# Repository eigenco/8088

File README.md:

# 8088
Modular standalone 8088 boards and BIOS.

There might be some redundancy that will be fixed later. 

Demo:  https://www.youtube.com/watch?v=A7xD_wg7Bzw

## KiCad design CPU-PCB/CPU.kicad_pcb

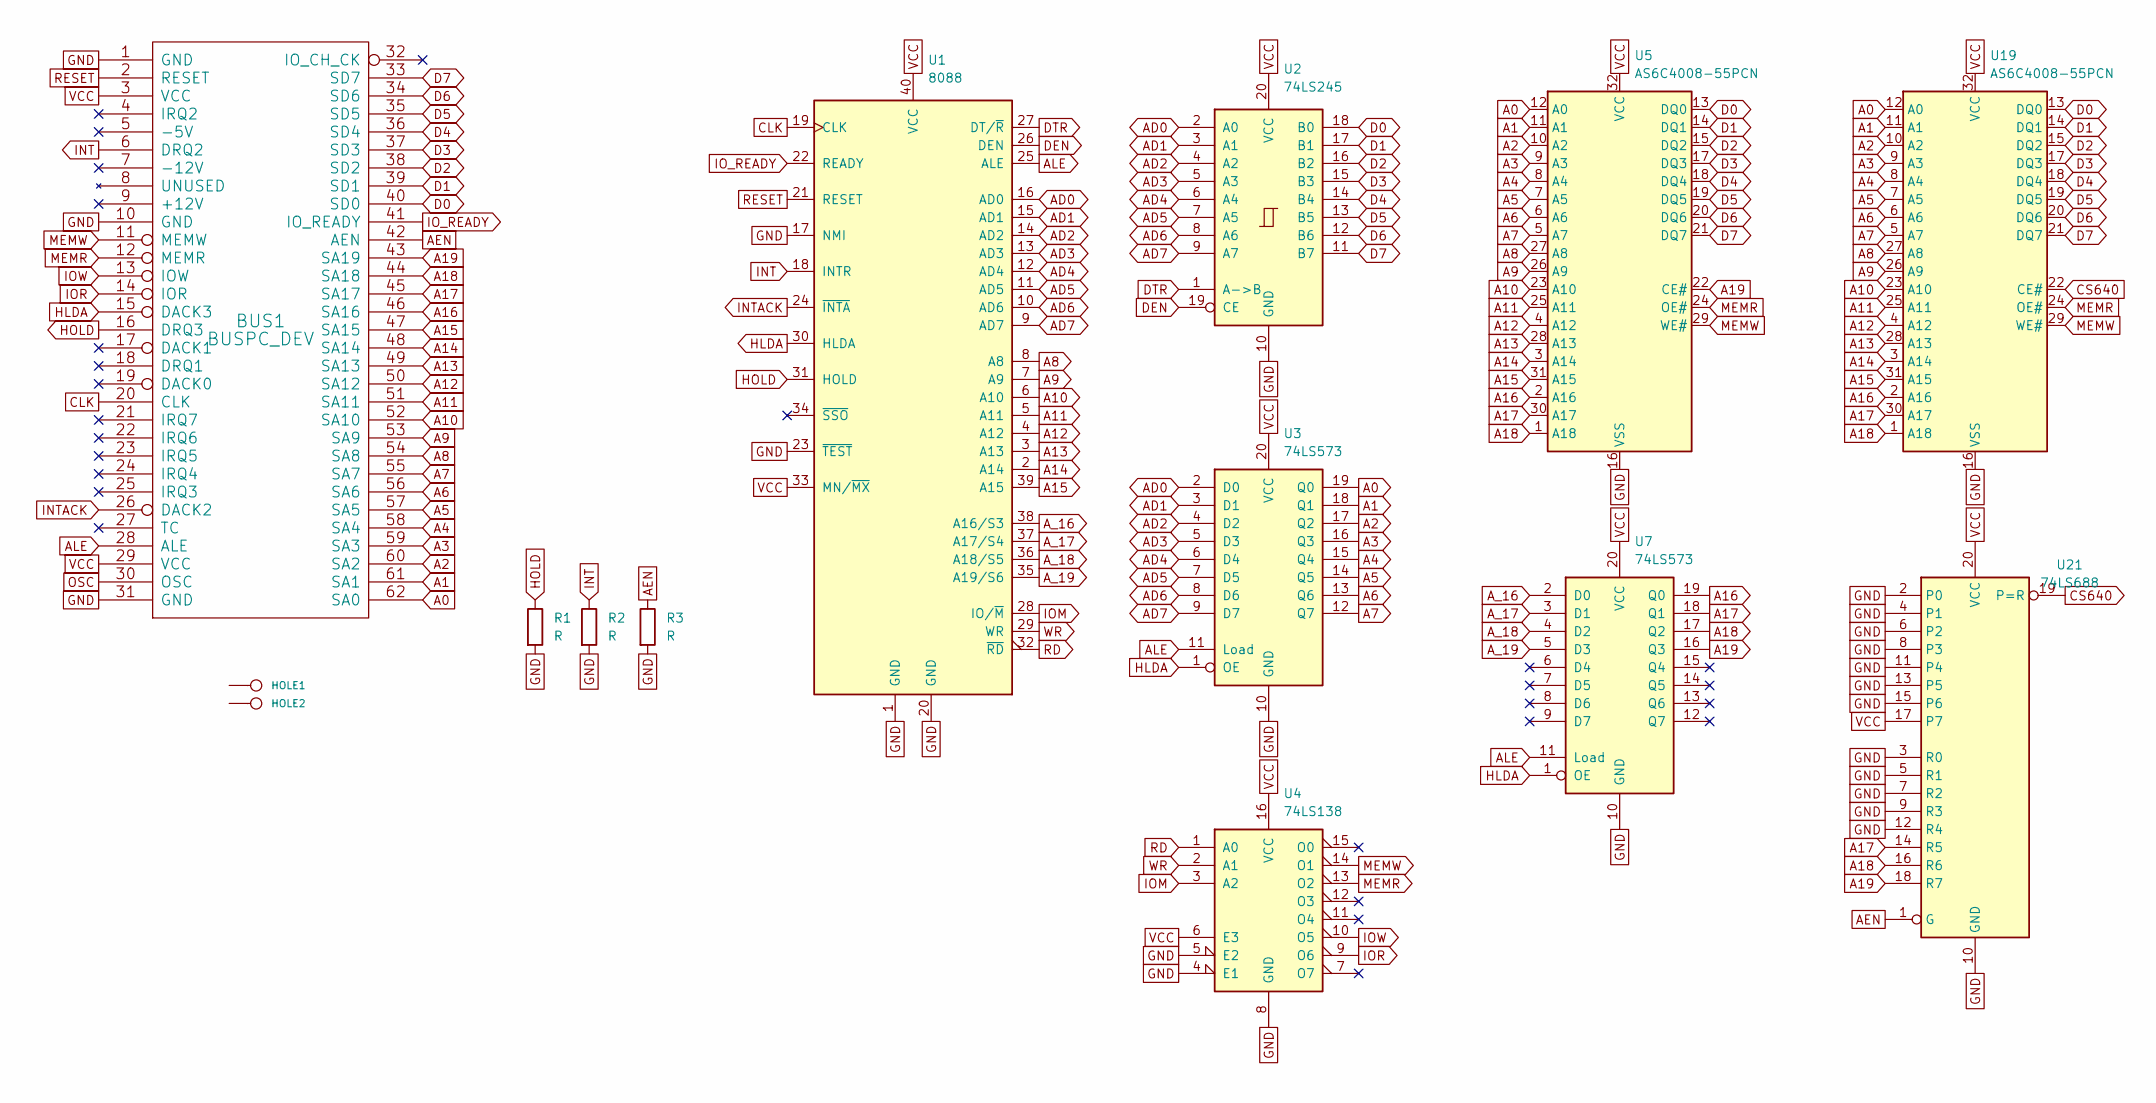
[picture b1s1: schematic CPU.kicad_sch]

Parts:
BUS1: BUSPC_DEV; Conn_Bus_ISA8
HOLE1, HOLE2: CONN_1; HOLE_3MM
R1, R2, R3: R; R_0201_0603Metric
U1: 8088; DIP-40_W15.24mm
U2: 74LS245; DIP-20_W7.62mm_Socket
U3, U7: 74LS573; DIP-20_W7.62mm_Socket
U4: 74LS138; DIP-16_W7.62mm_Socket
U5, U19: AS6C4008-55PCN; DIP-32_W15.24mm
U21: 74LS688; DIP-20_W7.62mm_Socket

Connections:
A0: BUS1.62 (SA0), U3.19 (Q0), U5.12 (A0), U19.12 (A0)
A1: BUS1.61 (SA1), U3.18 (Q1), U5.11 (A1), U19.11 (A1)
A2: BUS1.60 (SA2), U3.17 (Q2), U5.10 (A2), U19.10 (A2)
A3: BUS1.59 (SA3), U3.16 (Q3), U5.9 (A3), U19.9 (A3)
A4: BUS1.58 (SA4), U3.15 (Q4), U5.8 (A4), U19.8 (A4)
A5: BUS1.57 (SA5), U3.14 (Q5), U5.7 (A5), U19.7 (A5)
A6: BUS1.56 (SA6), U3.13 (Q6), U5.6 (A6), U19.6 (A6)
A7: BUS1.55 (SA7), U3.12 (Q7), U5.5 (A7), U19.5 (A7)
A8: BUS1.54 (SA8), U1.8 (A8), U5.27 (A8), U19.27 (A8)
A9: BUS1.53 (SA9), U1.7 (A9), U5.26 (A9), U19.26 (A9)
A10: BUS1.52 (SA10), U1.6 (A10), U5.23 (A10), U19.23 (A10)
A11: BUS1.51 (SA11), U1.5 (A11), U5.25 (A11), U19.25 (A11)
A12: BUS1.50 (SA12), U1.4 (A12), U5.4 (A12), U19.4 (A12)
A13: BUS1.49 (SA13), U1.3 (A13), U5.28 (A13), U19.28 (A13)
A14: BUS1.48 (SA14), U1.2 (A14), U5.3 (A14), U19.3 (A14)
A15: BUS1.47 (SA15), U1.39 (A15), U5.31 (A15), U19.31 (A15)
A16: BUS1.46 (SA16), U5.2 (A16), U7.19 (Q0), U19.2 (A16)
A17: BUS1.45 (SA17), U5.30 (A17), U7.18 (Q1), U19.30 (A17), U21.14 (R5)
A18: BUS1.44 (SA18), U5.1 (A18), U7.17 (Q2), U19.1 (A18), U21.16 (R6)
A19: BUS1.43 (SA19), U5.22 (CE#), U7.16 (Q3), U21.18 (R7)
AD0: U1.16 (AD0), U2.2 (A0), U3.2 (D0)
AD1: U1.15 (AD1), U2.3 (A1), U3.3 (D1)
AD2: U1.14 (AD2), U2.4 (A2), U3.4 (D2)
AD3: U1.13 (AD3), U2.5 (A3), U3.5 (D3)
AD4: U1.12 (AD4), U2.6 (A4), U3.6 (D4)
AD5: U1.11 (AD5), U2.7 (A5), U3.7 (D5)
AD6: U1.10 (AD6), U2.8 (A6), U3.8 (D6)
AD7: U1.9 (AD7), U2.9 (A7), U3.9 (D7)
AEN: BUS1.42 (AEN), R3.1, U21.1 (G)
ALE: BUS1.28 (ALE), U1.25 (ALE), U3.11 (Load), U7.11 (Load)
A_16: U1.38 (A16/S3), U7.2 (D0)
A_17: U1.37 (A17/S4), U7.3 (D1)
A_18: U1.36 (A18/S5), U7.4 (D2)
A_19: U1.35 (A19/S6), U7.5 (D3)
CLK: BUS1.20 (CLK), U1.19 (CLK)
CS640: U19.22 (CE#), U21.19 (P=R)
D0: BUS1.40 (SD0), U2.18 (B0), U5.13 (DQ0), U19.13 (DQ0)
D1: BUS1.39 (SD1), U2.17 (B1), U5.14 (DQ1), U19.14 (DQ1)
D2: BUS1.38 (SD2), U2.16 (B2), U5.15 (DQ2), U19.15 (DQ2)
D3: BUS1.37 (SD3), U2.15 (B3), U5.17 (DQ3), U19.17 (DQ3)
D4: BUS1.36 (SD4), U2.14 (B4), U5.18 (DQ4), U19.18 (DQ4)
D5: BUS1.35 (SD5), U2.13 (B5), U5.19 (DQ5), U19.19 (DQ5)
D6: BUS1.34 (SD6), U2.12 (B6), U5.20 (DQ6), U19.20 (DQ6)
D7: BUS1.33 (SD7), U2.11 (B7), U5.21 (DQ7), U19.21 (DQ7)
DEN: U1.26 (DEN), U2.19 (CE)
DTR: U1.27 (DT/~R), U2.1 (A->B)
GND: BUS1.1 (GND), BUS1.10 (GND), BUS1.31 (GND), R1.2, R2.2, R3.2, U1.1 (GND), U1.17 (NMI), U1.20 (GND), U1.23 (~TEST), U2.10 (GND), U3.10 (GND), U4.4 (E1), U4.5 (E2), U4.8 (GND), U5.16 (VSS), U7.10 (GND), U19.16 (VSS), U21.2 (P0), U21.3 (R0), U21.4 (P1), U21.5 (R1), U21.6 (P2), U21.7 (R2), U21.8 (P3), U21.9 (R3), U21.10 (GND), U21.11 (P4), U21.12 (R4), U21.13 (P5), U21.15 (P6)
HLDA: BUS1.15 (DACK3), U1.30 (HLDA), U3.1 (OE), U7.1 (OE)
HOLD: BUS1.16 (DRQ3), R1.1, U1.31 (HOLD)
INT: BUS1.6 (DRQ2), R2.1, U1.18 (INTR)
INTACK: BUS1.26 (DACK2), U1.24 (~INTA)
IOM: U1.28 (IO/~M), U4.3 (A2)
IOR: BUS1.14 (IOR), U4.9 (O6)
IOW: BUS1.13 (IOW), U4.10 (O5)
IO_READY: BUS1.41 (IO_READY), U1.22 (READY)
MEMR: BUS1.12 (MEMR), U4.13 (O2), U5.24 (OE#), U19.24 (OE#)
MEMW: BUS1.11 (MEMW), U4.14 (O1), U5.29 (WE#), U19.29 (WE#)
OSC: BUS1.30 (OSC)
RD: U1.32 (~RD), U4.1 (A0)
RESET: BUS1.2 (RESET), U1.21 (RESET)
VCC: BUS1.3 (VCC), BUS1.29 (VCC), U1.33 (MN/~MX), U1.40 (VCC), U2.20 (VCC), U3.20 (VCC), U4.6 (E3), U4.16 (VCC), U5.32 (VCC), U7.20 (VCC), U19.32 (VCC), U21.17 (P7), U21.20 (VCC)
WR: U1.29 (WR), U4.2 (A1)

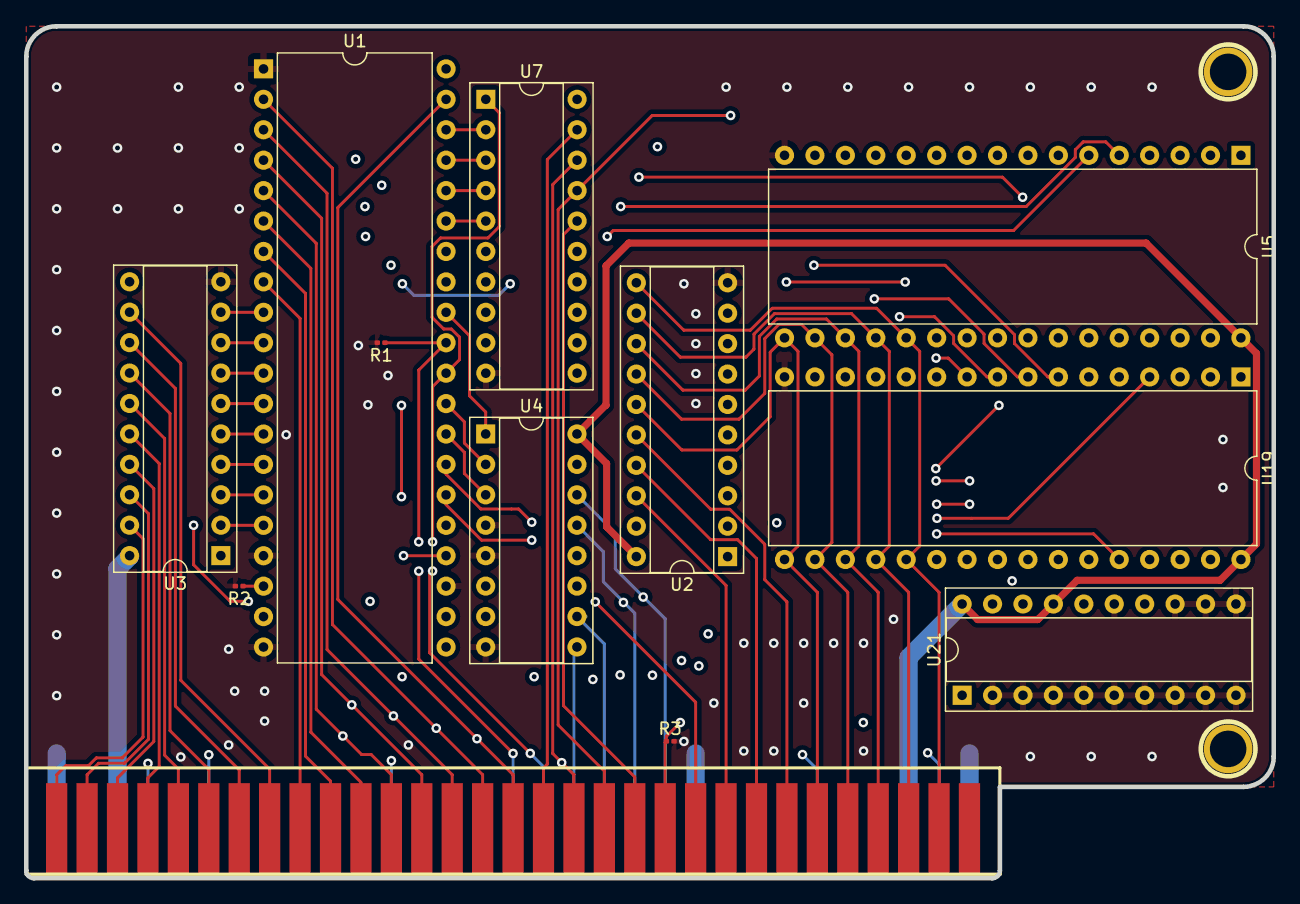
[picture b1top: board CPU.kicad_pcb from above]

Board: 4 copper layers, 104.1 x 71.1 mm, 14 parts (0 on the bottom side), 61 nets.

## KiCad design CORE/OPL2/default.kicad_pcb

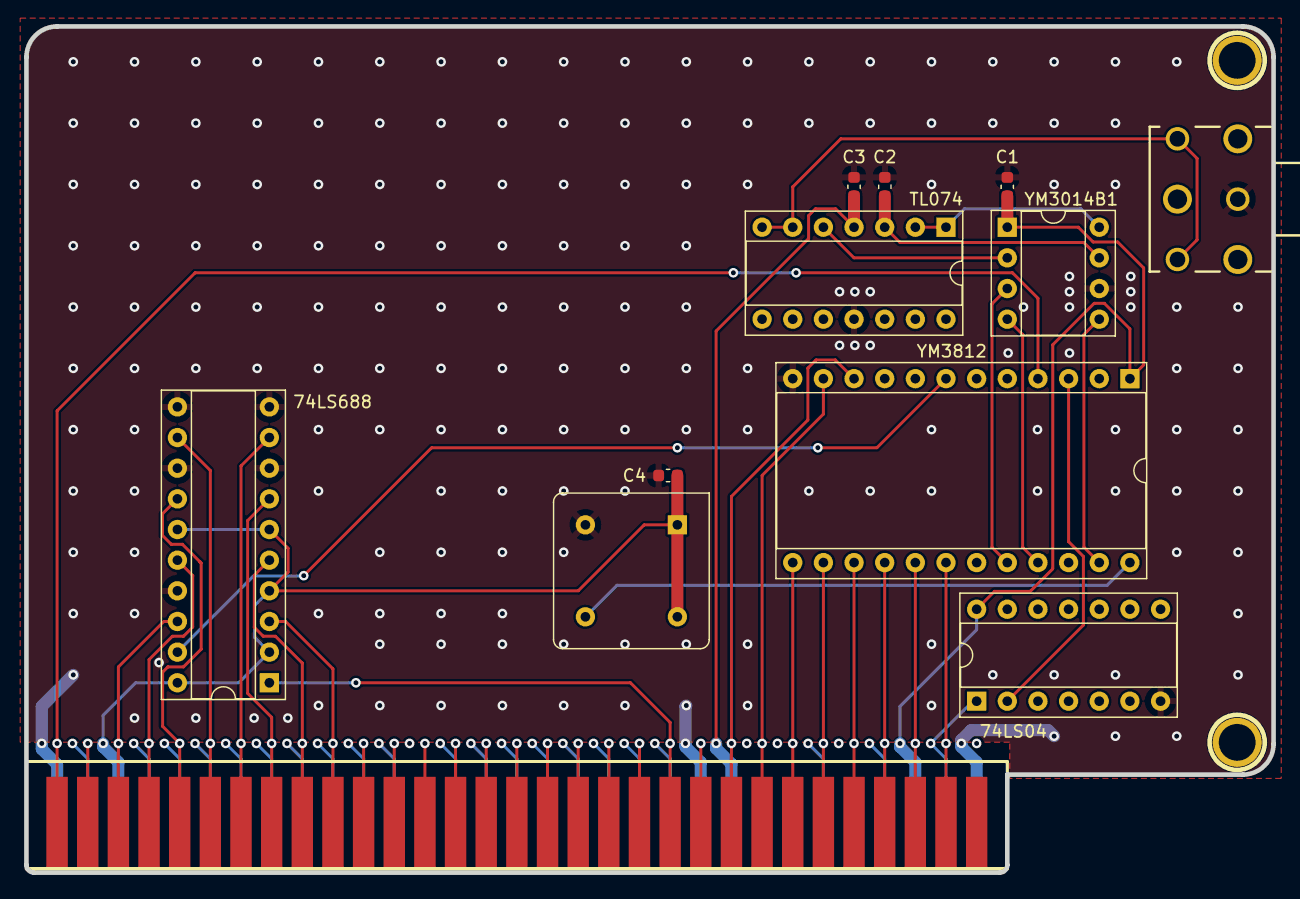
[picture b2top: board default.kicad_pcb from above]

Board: 4 copper layers, 103.3 x 70.1 mm, 14 parts (0 on the bottom side), 32 nets.

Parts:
74LS04: 74LS04; DIP-14_W7.62mm_Socket
74LS688: 74LS688; DIP-20_W7.62mm_Socket
C1, C2, C3, C4: 10uF; C_0603_1608Metric
HOLE1, HOLE2: CONN_1; HOLE_3MM
J1: Bus_ISA_8bit; Conn_Bus_ISA8
J3: Conn_02x03_Counter_Clockwise; STX31003N
TL074: TL074; DIP-14_W7.62mm_Socket
X1: CXO_DIP8; Oscillator_DIP-8
YM3014B1: Conn_02x04_Counter_Clockwise; DIP-8_W7.62mm_Socket
YM3812: Conn_02x12_Counter_Clockwise; DIP-24_W15.24mm_Socket

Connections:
A0: J1.62 (BA00), YM3812.4
A2: 74LS688.18 (R7), J1.60 (BA02)
A3: 74LS688.16 (R6), J1.59 (BA03)
A4: 74LS688.14 (R5), J1.58 (BA04)
A5: 74LS688.12 (R4), J1.57 (BA05)
A6: 74LS688.9 (R3), J1.56 (BA06)
A7: 74LS688.7 (R2), J1.55 (BA07)
A8: 74LS688.5 (R1), J1.54 (BA08)
A9: 74LS688.3 (R0), J1.53 (BA09)
AEN: 74LS688.1 (G), J1.42 (AEN)
CLK358: X1.5 (OUT), YM3812.24
D0: J1.40 (DB0), YM3812.10
D1: J1.39 (DB1), YM3812.11
D2: J1.38 (DB2), YM3812.13
D3: J1.37 (DB3), YM3812.14
D4: J1.36 (DB4), YM3812.15
D5: J1.35 (DB5), YM3812.16
D6: J1.34 (DB6), YM3812.17
D7: J1.33 (DB7), YM3812.18
DAC_CLK: YM3014B1.5, YM3812.23
DAC_DATA: YM3014B1.4, YM3812.21
DAC_SYNC: YM3014B1.3, YM3812.20
GND: 74LS04.7 (GND), 74LS688.8 (P3), 74LS688.10 (GND), 74LS688.11 (P4), 74LS688.13 (P5), 74LS688.17 (P7), C1.2, C2.2, C3.2, C4.2, HOLE1.1, HOLE2.1, J1.1 (GND), J1.10 (GND), J1.31 (GND), J3.1, TL074.11 (V-), X1.4 (GND), YM3014B1.6, YM3812.12
MP: TL074.1, TL074.2 (-), YM3014B1.8
OUT: J3.2, J3.5, TL074.6 (-), TL074.7
RB: C2.1, TL074.3 (+), YM3014B1.7
RESET: 74LS04.1, J1.2 (RESET)
ToBUFF: TL074.5 (+), YM3014B1.2
VCC: 74LS04.14 (VCC), 74LS688.2 (P0), 74LS688.4 (P1), 74LS688.6 (P2), 74LS688.15 (P6), 74LS688.20 (VCC), C1.1, C4.1, J1.3 (VCC), J1.29 (VCC), X1.1 (EN), X1.8 (Vcc), YM3014B1.1, YM3812.1
VP: C3.1, J1.9 (+12V), TL074.4 (V+)
~CS: 74LS688.19 (P=R), YM3812.7
~RESET: 74LS04.2, YM3812.3

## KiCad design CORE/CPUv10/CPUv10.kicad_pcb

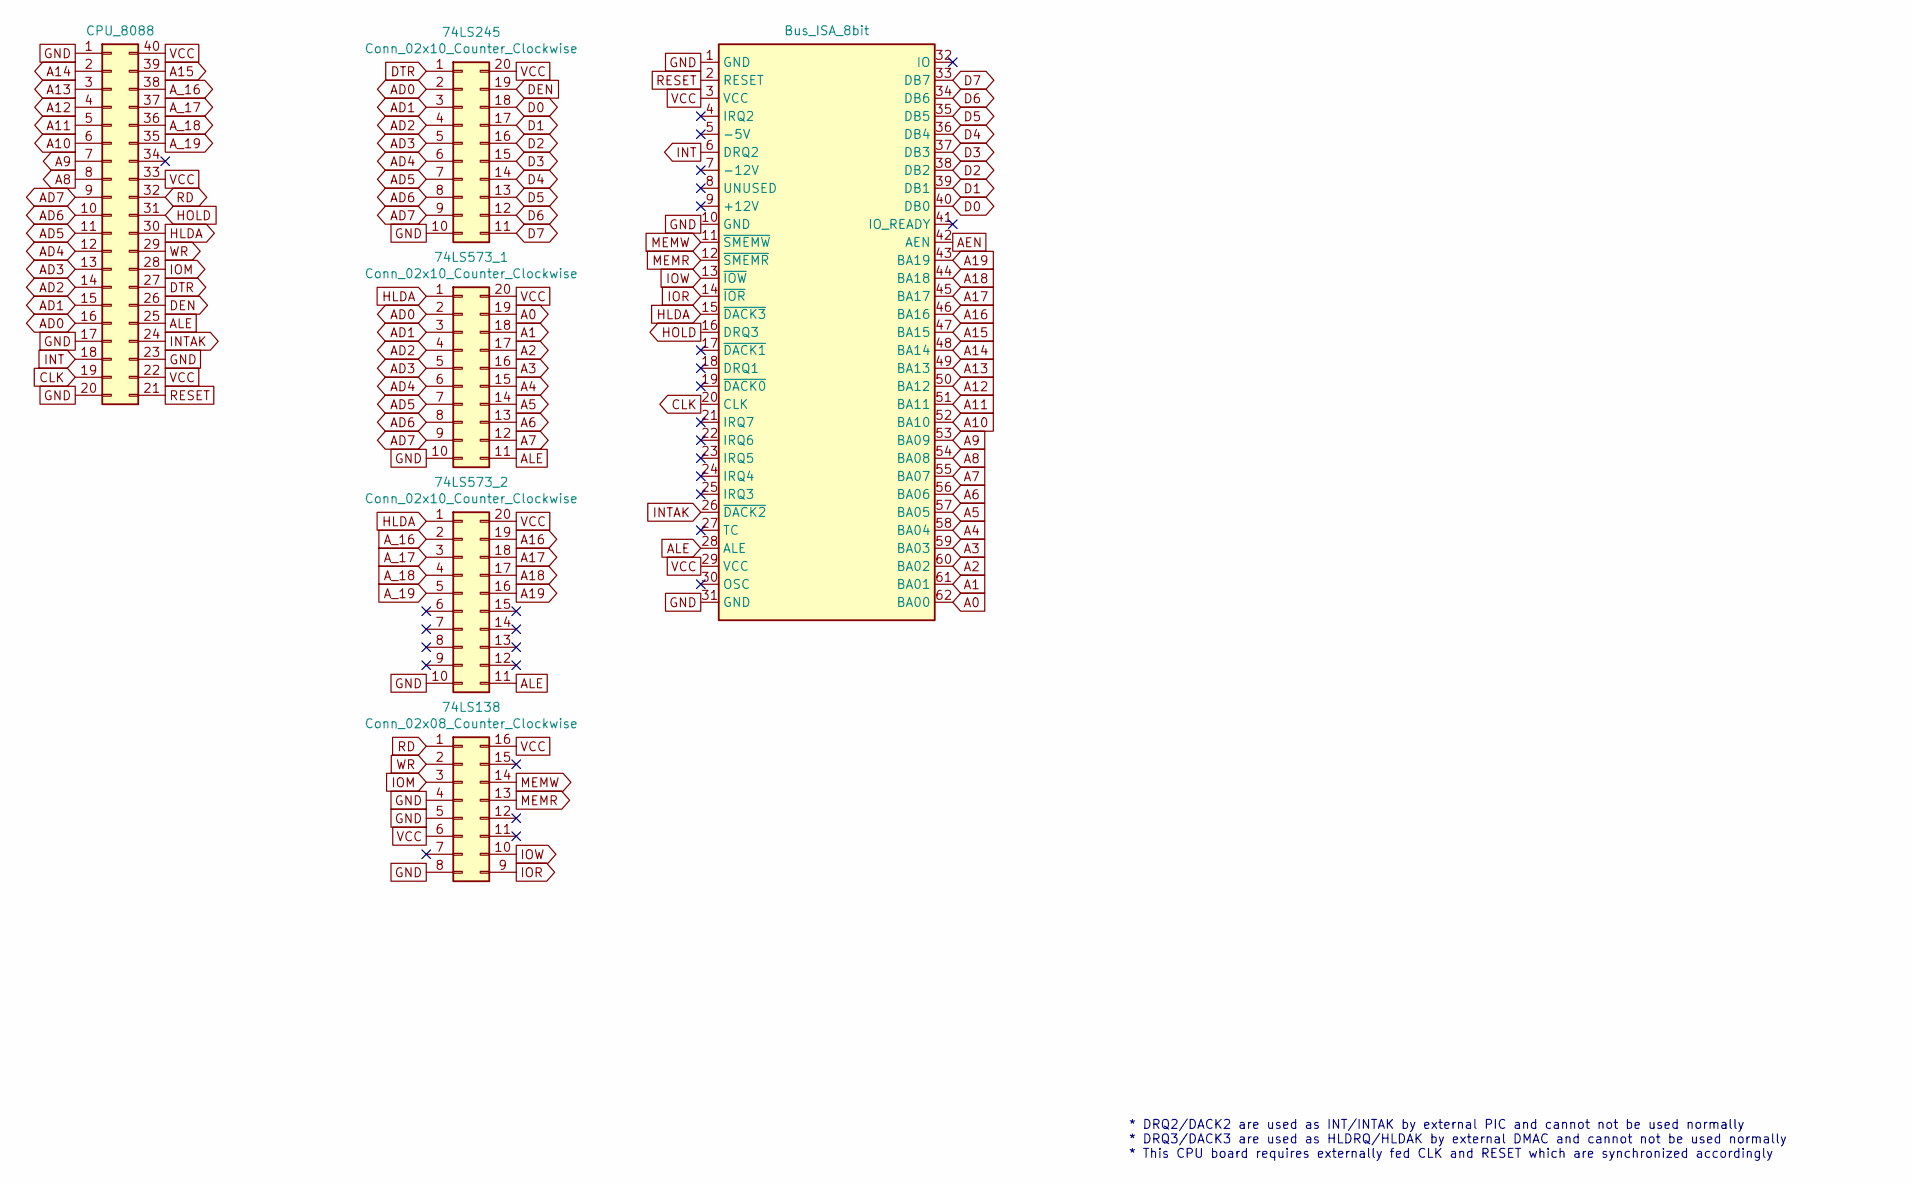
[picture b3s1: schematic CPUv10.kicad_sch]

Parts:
74LS138: Conn_02x08_Counter_Clockwise; DIP-16_W7.62mm_Socket
74LS245, 74LS573_1, 74LS573_2: Conn_02x10_Counter_Clockwise; DIP-20_W7.62mm_Socket
CPU_8088: Conn_02x20_Counter_Clockwise; DIP-40_W15.24mm_Socket_LongPads
J4: Bus_ISA_8bit; BUS_PC

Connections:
A0: 74LS573_1.19, J4.62 (BA00)
A1: 74LS573_1.18, J4.61 (BA01)
A2: 74LS573_1.17, J4.60 (BA02)
A3: 74LS573_1.16, J4.59 (BA03)
A4: 74LS573_1.15, J4.58 (BA04)
A5: 74LS573_1.14, J4.57 (BA05)
A6: 74LS573_1.13, J4.56 (BA06)
A7: 74LS573_1.12, J4.55 (BA07)
A8: CPU_8088.8, J4.54 (BA08)
A9: CPU_8088.7, J4.53 (BA09)
A10: CPU_8088.6, J4.52 (BA10)
A11: CPU_8088.5, J4.51 (BA11)
A12: CPU_8088.4, J4.50 (BA12)
A13: CPU_8088.3, J4.49 (BA13)
A14: CPU_8088.2, J4.48 (BA14)
A15: CPU_8088.39, J4.47 (BA15)
A16: 74LS573_2.19, J4.46 (BA16)
A17: 74LS573_2.18, J4.45 (BA17)
A18: 74LS573_2.17, J4.44 (BA18)
A19: 74LS573_2.16, J4.43 (BA19)
AD0: 74LS245.2, 74LS573_1.2, CPU_8088.16
AD1: 74LS245.3, 74LS573_1.3, CPU_8088.15
AD2: 74LS245.4, 74LS573_1.4, CPU_8088.14
AD3: 74LS245.5, 74LS573_1.5, CPU_8088.13
AD4: 74LS245.6, 74LS573_1.6, CPU_8088.12
AD5: 74LS245.7, 74LS573_1.7, CPU_8088.11
AD6: 74LS245.8, 74LS573_1.8, CPU_8088.10
AD7: 74LS245.9, 74LS573_1.9, CPU_8088.9
AEN: J4.42 (AEN)
ALE: 74LS573_1.11, 74LS573_2.11, CPU_8088.25, J4.28 (ALE)
A_16: 74LS573_2.2, CPU_8088.38
A_17: 74LS573_2.3, CPU_8088.37
A_18: 74LS573_2.4, CPU_8088.36
A_19: 74LS573_2.5, CPU_8088.35
CLK: CPU_8088.19, J4.20 (CLK)
D0: 74LS245.18, J4.40 (DB0)
D1: 74LS245.17, J4.39 (DB1)
D2: 74LS245.16, J4.38 (DB2)
D3: 74LS245.15, J4.37 (DB3)
D4: 74LS245.14, J4.36 (DB4)
D5: 74LS245.13, J4.35 (DB5)
D6: 74LS245.12, J4.34 (DB6)
D7: 74LS245.11, J4.33 (DB7)
DEN: 74LS245.19, CPU_8088.26
DTR: 74LS245.1, CPU_8088.27
GND: 74LS138.4, 74LS138.5, 74LS138.8, 74LS245.10, 74LS573_1.10, 74LS573_2.10, CPU_8088.1, CPU_8088.17, CPU_8088.20, CPU_8088.23, J4.1 (GND), J4.10 (GND), J4.31 (GND)
HLDA: 74LS573_1.1, 74LS573_2.1, CPU_8088.30, J4.15 (~DACK3)
HOLD: CPU_8088.31, J4.16 (DRQ3)
INT: CPU_8088.18, J4.6 (DRQ2)
INTAK: CPU_8088.24, J4.26 (~DACK2)
IOM: 74LS138.3, CPU_8088.28
IOR: 74LS138.9, J4.14 (~IOR)
IOW: 74LS138.10, J4.13 (~IOW)
MEMR: 74LS138.13, J4.12 (~SMEMR)
MEMW: 74LS138.14, J4.11 (~SMEMW)
RD: 74LS138.1, CPU_8088.32
RESET: CPU_8088.21, J4.2 (RESET)
VCC: 74LS138.6, 74LS138.16, 74LS245.20, 74LS573_1.20, 74LS573_2.20, CPU_8088.22, CPU_8088.33, CPU_8088.40, J4.3 (VCC), J4.29 (VCC)
WR: 74LS138.2, CPU_8088.29

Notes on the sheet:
* DRQ2/DACK2 are used as INT/INTAK by external PIC and cannot not be used normally * DRQ3/DACK3 are used as HLDRQ/HLDAK by external DMAC and cannot not be used normally * This CPU board requires externally fed CLK and RESET which are synchronized accordingly

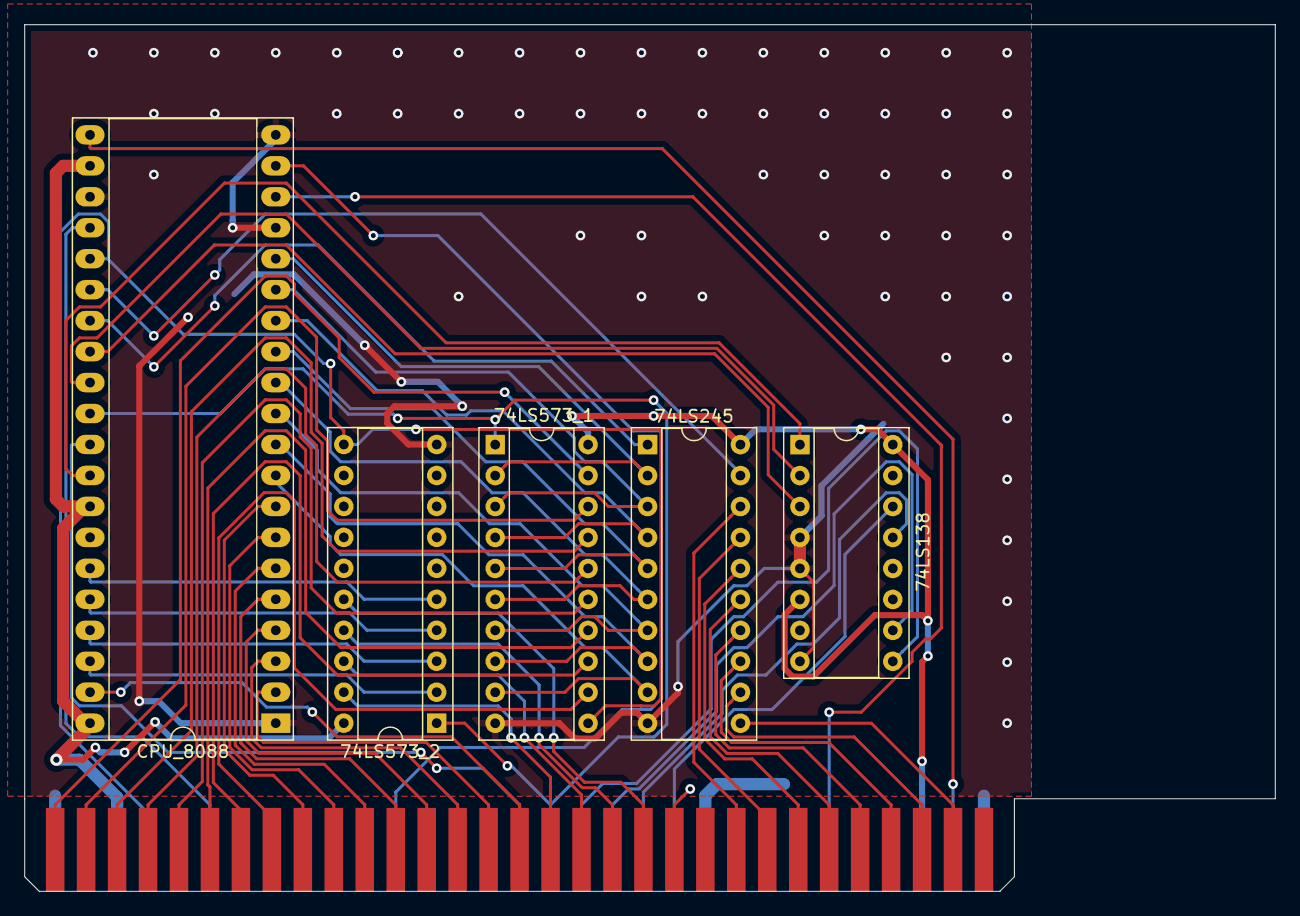
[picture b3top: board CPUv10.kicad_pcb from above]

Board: 2 copper layers, 102.6 x 71.1 mm, 6 parts (0 on the bottom side), 58 nets.

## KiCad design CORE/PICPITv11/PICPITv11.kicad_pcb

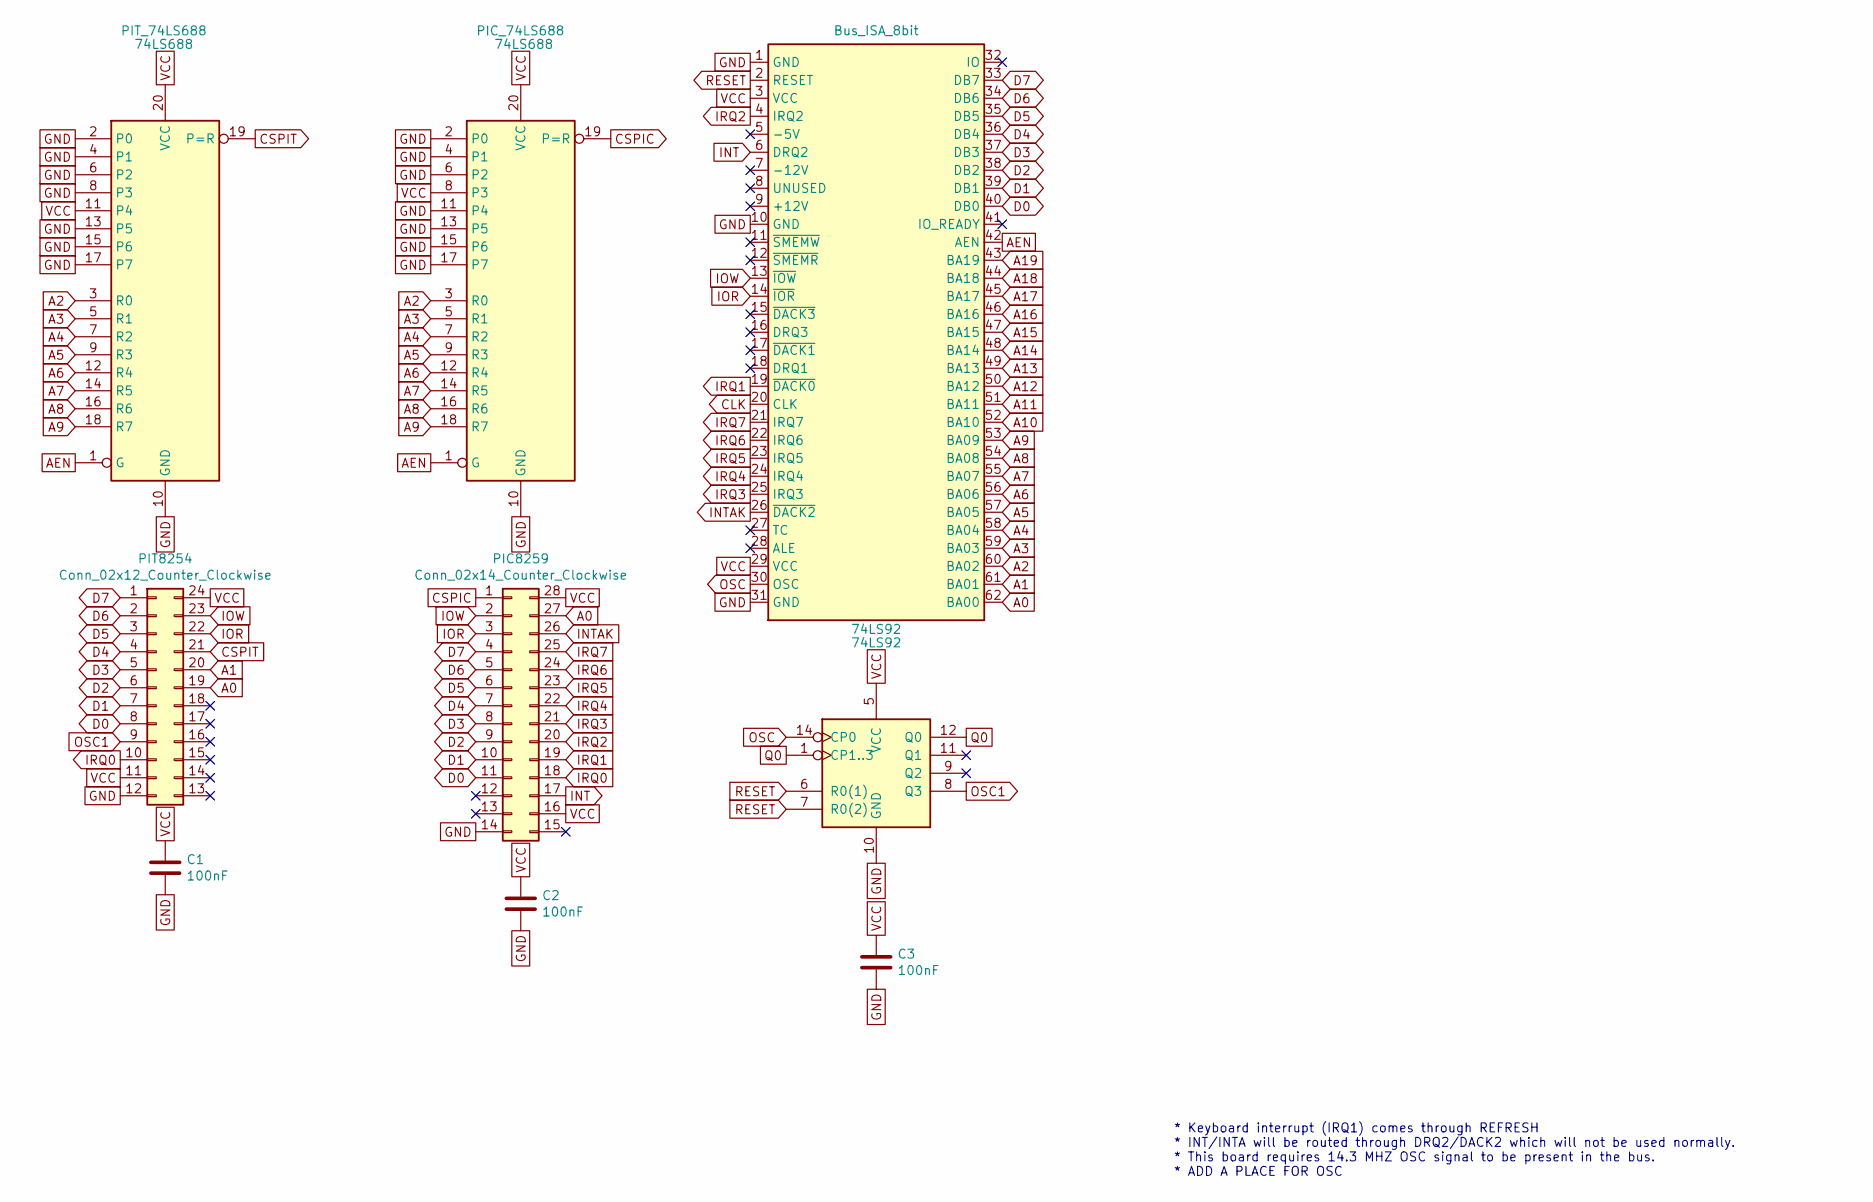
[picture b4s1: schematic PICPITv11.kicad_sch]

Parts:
74LS92: 74LS92; DIP-14_W7.62mm_Socket
C1, C2, C3: 100nF; C_0603_1608Metric
J4: Bus_ISA_8bit; BUS_PC
PIC8259: Conn_02x14_Counter_Clockwise; DIP-28_W15.24mm_Socket
PIC_74LS688: 74LS688; DIP-20_W7.62mm_Socket
PIT8254: Conn_02x12_Counter_Clockwise; DIP-24_W15.24mm_Socket
PIT_74LS688: 74LS688; DIP-20_W7.62mm_Socket

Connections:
A0: J4.62 (BA00), PIC8259.27, PIT8254.19
A1: J4.61 (BA01), PIT8254.20
A2: J4.60 (BA02), PIC_74LS688.3 (R0), PIT_74LS688.3 (R0)
A3: J4.59 (BA03), PIC_74LS688.5 (R1), PIT_74LS688.5 (R1)
A4: J4.58 (BA04), PIC_74LS688.7 (R2), PIT_74LS688.7 (R2)
A5: J4.57 (BA05), PIC_74LS688.9 (R3), PIT_74LS688.9 (R3)
A6: J4.56 (BA06), PIC_74LS688.12 (R4), PIT_74LS688.12 (R4)
A7: J4.55 (BA07), PIC_74LS688.14 (R5), PIT_74LS688.14 (R5)
A8: J4.54 (BA08), PIC_74LS688.16 (R6), PIT_74LS688.16 (R6)
A9: J4.53 (BA09), PIC_74LS688.18 (R7), PIT_74LS688.18 (R7)
A10: J4.52 (BA10)
A11: J4.51 (BA11)
A12: J4.50 (BA12)
A13: J4.49 (BA13)
A14: J4.48 (BA14)
A15: J4.47 (BA15)
A16: J4.46 (BA16)
A17: J4.45 (BA17)
A18: J4.44 (BA18)
A19: J4.43 (BA19)
AEN: J4.42 (AEN), PIC_74LS688.1 (G), PIT_74LS688.1 (G)
CLK: J4.20 (CLK)
CSPIC: PIC8259.1, PIC_74LS688.19 (P=R)
CSPIT: PIT8254.21, PIT_74LS688.19 (P=R)
D0: J4.40 (DB0), PIC8259.11, PIT8254.8
D1: J4.39 (DB1), PIC8259.10, PIT8254.7
D2: J4.38 (DB2), PIC8259.9, PIT8254.6
D3: J4.37 (DB3), PIC8259.8, PIT8254.5
D4: J4.36 (DB4), PIC8259.7, PIT8254.4
D5: J4.35 (DB5), PIC8259.6, PIT8254.3
D6: J4.34 (DB6), PIC8259.5, PIT8254.2
D7: J4.33 (DB7), PIC8259.4, PIT8254.1
INT: J4.6 (DRQ2), PIC8259.17
INTAK: J4.26 (~DACK2), PIC8259.26
IOR: J4.14 (~IOR), PIC8259.3, PIT8254.22
IOW: J4.13 (~IOW), PIC8259.2, PIT8254.23
IRQ0: PIC8259.18, PIT8254.10
IRQ2: J4.4 (IRQ2), PIC8259.20
IRQ3: J4.25 (IRQ3), PIC8259.21
IRQ5: J4.23 (IRQ5), PIC8259.23
IRQ6: J4.22 (IRQ6), PIC8259.24
IRQ7: J4.21 (IRQ7), PIC8259.25
OSC: 74LS92.14 (CP0), J4.30 (OSC)
OSC1: 74LS92.8 (Q3), PIT8254.9
Q0: 74LS92.1 (CP1..3), 74LS92.12 (Q0)
RESET: 74LS92.6 (R0(1)), 74LS92.7 (R0(2)), J4.2 (RESET)
VCC: 74LS92.5 (VCC), C1.1, C2.1, C3.1, J4.3 (VCC), J4.29 (VCC), PIC8259.16, PIC8259.28, PIC_74LS688.8 (P3), PIC_74LS688.20 (VCC), PIT8254.11, PIT8254.24, PIT_74LS688.11 (P4), PIT_74LS688.20 (VCC)

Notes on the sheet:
* Keyboard interrupt (IRQ1) comes through REFRESH * INT/INTA will be routed through DRQ2/DACK2 which will not be used normally. * This board requires 14.3 MHZ OSC signal to be present in the bus. * ADD A PLACE FOR OSC

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
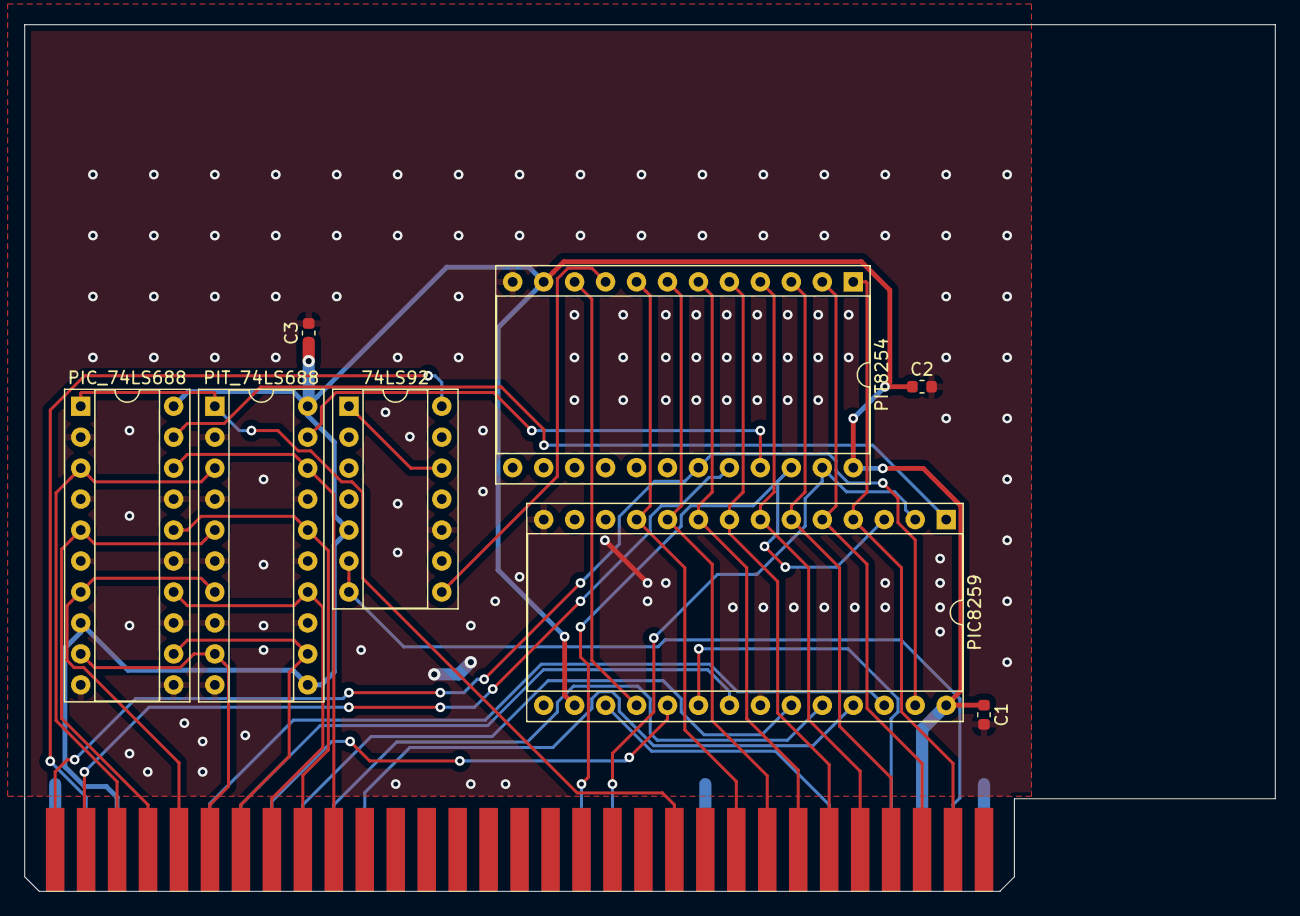
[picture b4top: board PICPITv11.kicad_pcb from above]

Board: 2 copper layers, 102.6 x 71.1 mm, 9 parts (0 on the bottom side), 38 nets.
